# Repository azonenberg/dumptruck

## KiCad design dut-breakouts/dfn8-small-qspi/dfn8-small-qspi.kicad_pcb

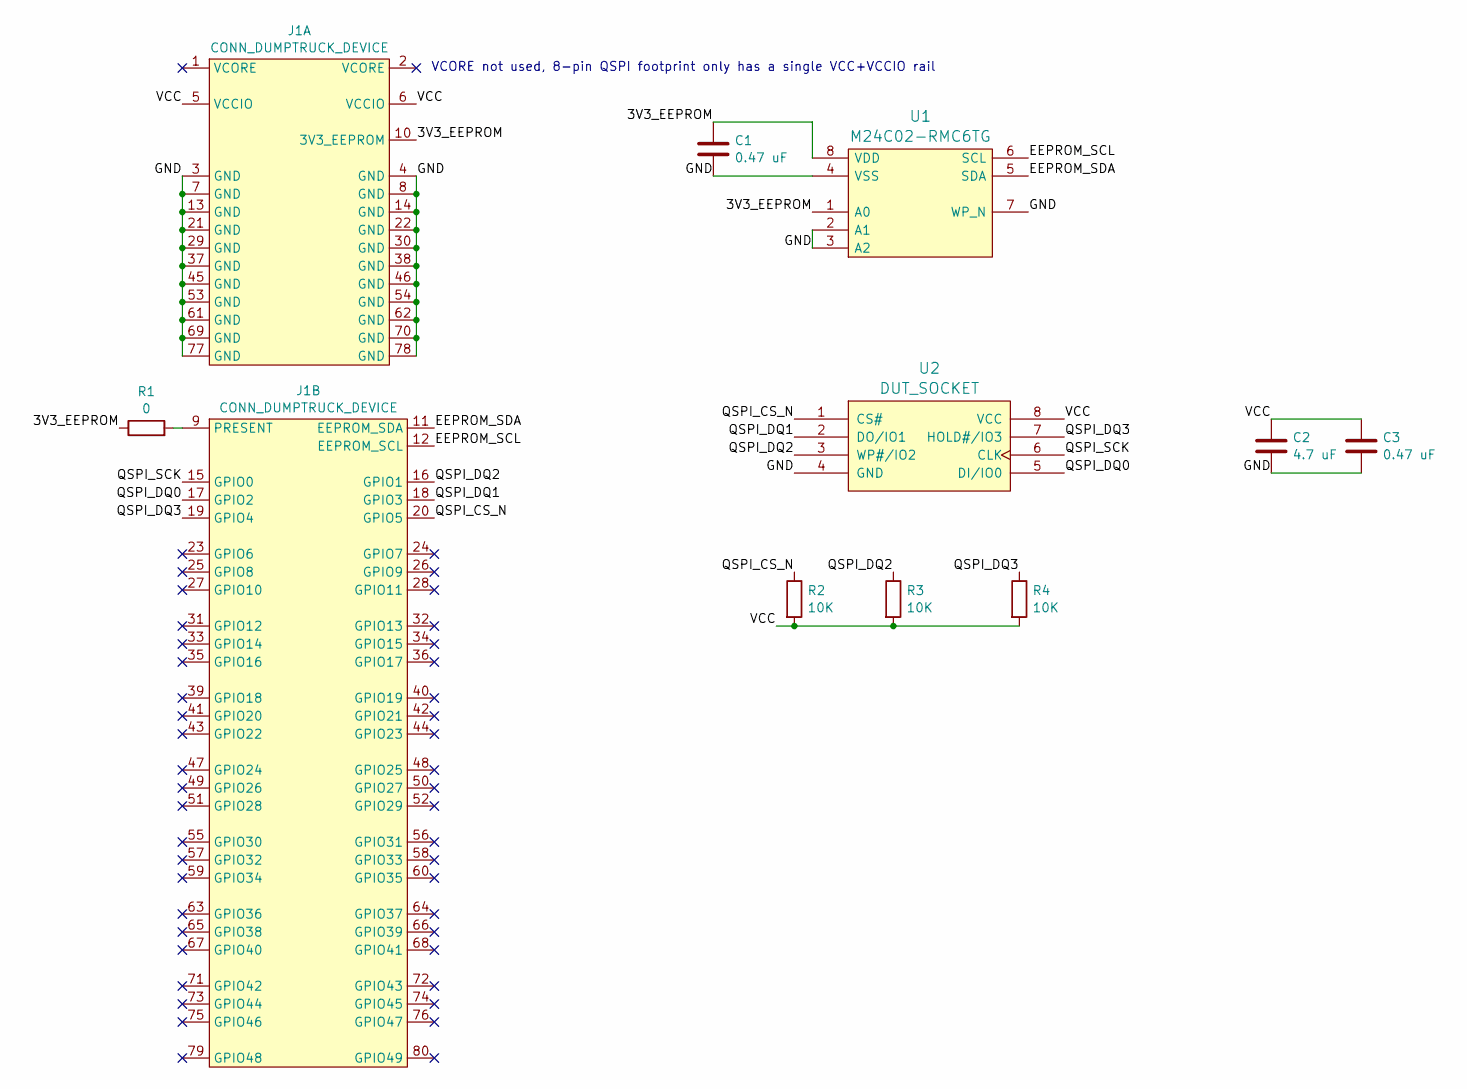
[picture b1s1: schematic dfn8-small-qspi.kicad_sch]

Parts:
C1, C3: 0.47 uF; EIA_0402_CAP_NOSILK
C2: 4.7 uF; EIA_0603_CAP_NOSILK
J1: CONN_DUMPTRUCK_DEVICE; CONN_SAMTEC_BSE-040-01-L-D-A-TR
R1: 0; EIA_0402_RES_NOSILK
R2, R3, R4: 10K; EIA_0402_RES_NOSILK
U1: M24C02-RMC6TG; DFN_8_0.5MM_2x3MM_TALL
U2: DUT_SOCKET; DFN_8_SOCKET_MOLDED_5x6MM

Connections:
/3V3_EEPROM: C1.1, J1.10 (3V3_EEPROM), R1.1, U1.1 (A0), U1.8 (VDD)
/EEPROM_SCL: J1.12 (EEPROM_SCL), U1.6 (SCL)
/EEPROM_SDA: J1.11 (EEPROM_SDA), U1.5 (SDA)
/GND: C1.2, C2.2, C3.2, J1.3 (GND), J1.4 (GND), J1.7 (GND), J1.8 (GND), J1.13 (GND), J1.14 (GND), J1.21 (GND), J1.22 (GND), J1.29 (GND), J1.30 (GND), J1.37 (GND), J1.38 (GND), J1.45 (GND), J1.46 (GND), J1.53 (GND), J1.54 (GND), J1.61 (GND), J1.62 (GND), J1.69 (GND), J1.70 (GND), J1.77 (GND), J1.78 (GND), U1.2 (A1), U1.3 (A2), U1.4 (VSS), U1.7 (WP_N), U2.4 (GND)
/QSPI_CS_N: J1.20 (GPIO5), R2.1, U2.1 (CS#)
/QSPI_DQ0: J1.17 (GPIO2), U2.5 (DI/IO0)
/QSPI_DQ1: J1.18 (GPIO3), U2.2 (DO/IO1)
/QSPI_DQ2: J1.16 (GPIO1), R3.1, U2.3 (WP#/IO2)
/QSPI_DQ3: J1.19 (GPIO4), R4.1, U2.7 (HOLD#/IO3)
/QSPI_SCK: J1.15 (GPIO0), U2.6 (CLK)
/VCC: C2.1, C3.1, J1.5 (VCCIO), J1.6 (VCCIO), R2.2, R3.2, R4.2, U2.8 (VCC)
unnamed: J1.9 (PRESENT), R1.2

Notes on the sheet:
VCORE not used, 8-pin QSPI footprint only has a single VCC+VCCIO rail

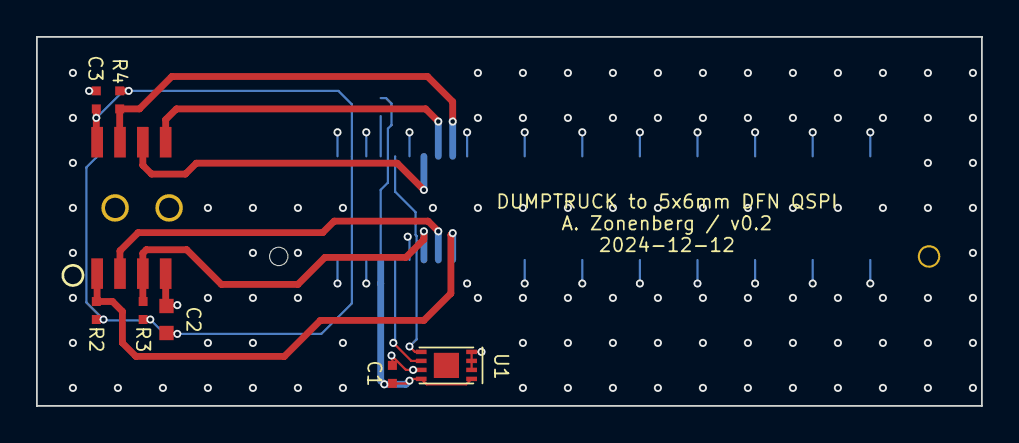
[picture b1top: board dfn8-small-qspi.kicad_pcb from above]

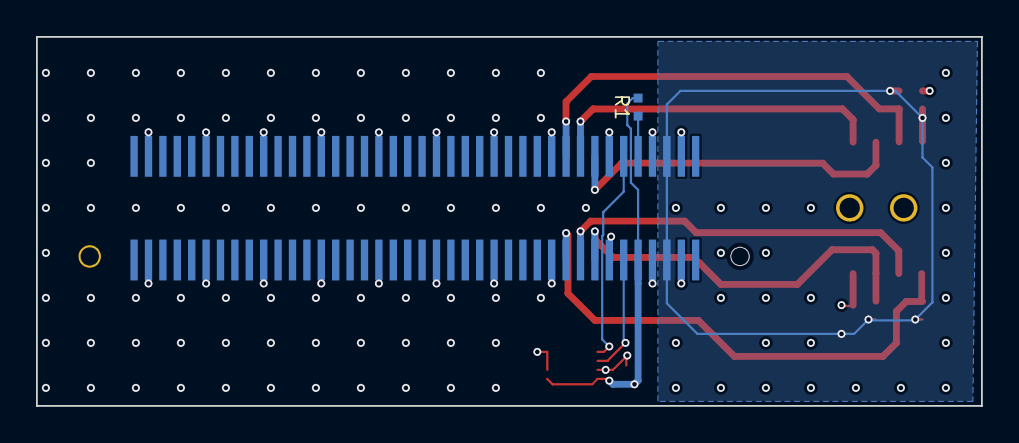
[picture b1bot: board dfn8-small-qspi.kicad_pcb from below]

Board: 4 copper layers, 52.5 x 20.5 mm, 10 parts (2 on the bottom side), 12 nets.

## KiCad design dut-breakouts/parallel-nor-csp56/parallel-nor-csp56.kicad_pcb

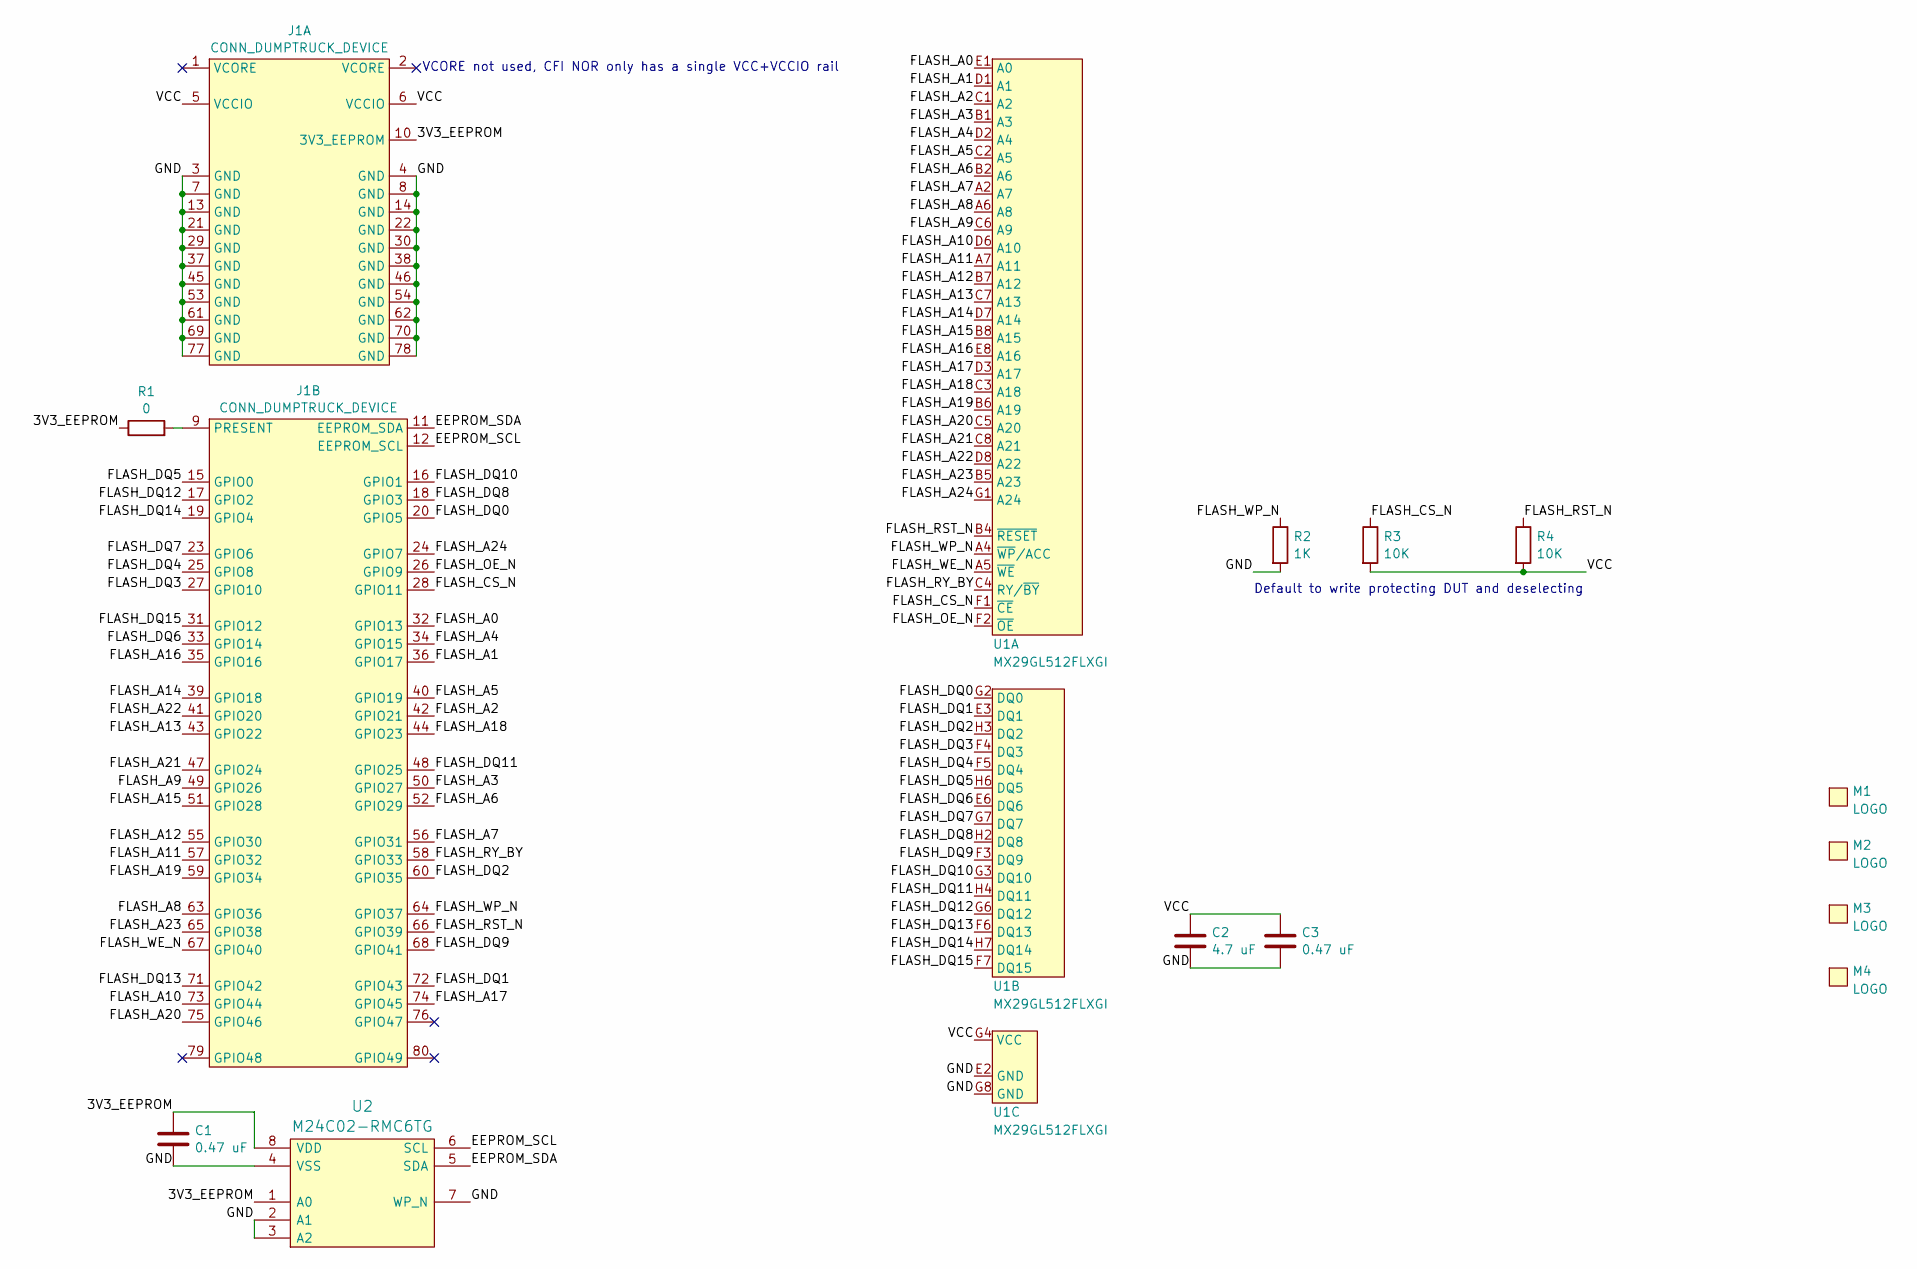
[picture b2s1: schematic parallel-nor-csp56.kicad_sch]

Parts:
C1, C3: 0.47 uF; EIA_0402_CAP_NOSILK
C2: 4.7 uF; EIA_0603_CAP_NOSILK
J1: CONN_DUMPTRUCK_DEVICE; CONN_SAMTEC_BSE-040-01-L-D-A-TR
M1: LOGO; LONGTHING-1200DPI
M2: LOGO; Logo_silk_ROHS_5x2.8mm
M3: LOGO; Logo_silk_OSHW_6x6mm
M4: LOGO; Logo_silk_WEEE_3.4x5mm
R1: 0; EIA_0402_RES_NOSILK
R2: 1K; EIA_0402_RES_NOSILK
R3, R4: 10K; EIA_0402_RES_NOSILK
U1: MX29GL512FLXGI; BGA_56_6x9_DEPOP_0.8MM_CFI_CSP
U2: M24C02-RMC6TG; DFN_8_0.5MM_2x3MM_TALL

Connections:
/3V3_EEPROM: C1.1, J1.10 (3V3_EEPROM), R1.1, U2.1 (A0), U2.8 (VDD)
/EEPROM_SCL: J1.12 (EEPROM_SCL), U2.6 (SCL)
/EEPROM_SDA: J1.11 (EEPROM_SDA), U2.5 (SDA)
/FLASH_A0: J1.32 (GPIO13), U1.E1 (A0)
/FLASH_A1: J1.36 (GPIO17), U1.D1 (A1)
/FLASH_A2: J1.42 (GPIO21), U1.C1 (A2)
/FLASH_A3: J1.50 (GPIO27), U1.B1 (A3)
/FLASH_A4: J1.34 (GPIO15), U1.D2 (A4)
/FLASH_A5: J1.40 (GPIO19), U1.C2 (A5)
/FLASH_A6: J1.52 (GPIO29), U1.B2 (A6)
/FLASH_A7: J1.56 (GPIO31), U1.A2 (A7)
/FLASH_A8: J1.63 (GPIO36), U1.A6 (A8)
/FLASH_A9: J1.49 (GPIO26), U1.C6 (A9)
/FLASH_A10: J1.73 (GPIO44), U1.D6 (A10)
/FLASH_A11: J1.57 (GPIO32), U1.A7 (A11)
/FLASH_A12: J1.55 (GPIO30), U1.B7 (A12)
/FLASH_A13: J1.43 (GPIO22), U1.C7 (A13)
/FLASH_A14: J1.39 (GPIO18), U1.D7 (A14)
/FLASH_A15: J1.51 (GPIO28), U1.B8 (A15)
/FLASH_A16: J1.35 (GPIO16), U1.E8 (A16)
/FLASH_A17: J1.74 (GPIO45), U1.D3 (A17)
/FLASH_A18: J1.44 (GPIO23), U1.C3 (A18)
/FLASH_A19: J1.59 (GPIO34), U1.B6 (A19)
/FLASH_A20: J1.75 (GPIO46), U1.C5 (A20)
/FLASH_A21: J1.47 (GPIO24), U1.C8 (A21)
/FLASH_A22: J1.41 (GPIO20), U1.D8 (A22)
/FLASH_A23: J1.65 (GPIO38), U1.B5 (A23)
/FLASH_A24: J1.24 (GPIO7), U1.G1 (A24)
/FLASH_CS_N: J1.28 (GPIO11), R3.1, U1.F1 (~CE)
/FLASH_DQ0: J1.20 (GPIO5), U1.G2 (DQ0)
/FLASH_DQ1: J1.72 (GPIO43), U1.E3 (DQ1)
/FLASH_DQ2: J1.60 (GPIO35), U1.H3 (DQ2)
/FLASH_DQ3: J1.27 (GPIO10), U1.F4 (DQ3)
/FLASH_DQ4: J1.25 (GPIO8), U1.F5 (DQ4)
/FLASH_DQ5: J1.15 (GPIO0), U1.H6 (DQ5)
/FLASH_DQ6: J1.33 (GPIO14), U1.E6 (DQ6)
/FLASH_DQ7: J1.23 (GPIO6), U1.G7 (DQ7)
/FLASH_DQ8: J1.18 (GPIO3), U1.H2 (DQ8)
/FLASH_DQ9: J1.68 (GPIO41), U1.F3 (DQ9)
/FLASH_DQ10: J1.16 (GPIO1), U1.G3 (DQ10)
/FLASH_DQ11: J1.48 (GPIO25), U1.H4 (DQ11)
/FLASH_DQ12: J1.17 (GPIO2), U1.G6 (DQ12)
/FLASH_DQ13: J1.71 (GPIO42), U1.F6 (DQ13)
/FLASH_DQ14: J1.19 (GPIO4), U1.H7 (DQ14)
/FLASH_DQ15: J1.31 (GPIO12), U1.F7 (DQ15)
/FLASH_OE_N: J1.26 (GPIO9), U1.F2 (~OE)
/FLASH_RST_N: J1.66 (GPIO39), R4.1, U1.B4 (~RESET)
/FLASH_RY_BY: J1.58 (GPIO33), U1.C4 (RY/~BY)
/FLASH_WE_N: J1.67 (GPIO40), U1.A5 (~WE)
/FLASH_WP_N: J1.64 (GPIO37), R2.1, U1.A4 (~WP/ACC)
/GND: C1.2, C2.2, C3.2, J1.3 (GND), J1.4 (GND), J1.7 (GND), J1.8 (GND), J1.13 (GND), J1.14 (GND), J1.21 (GND), J1.22 (GND), J1.29 (GND), J1.30 (GND), J1.37 (GND), J1.38 (GND), J1.45 (GND), J1.46 (GND), J1.53 (GND), J1.54 (GND), J1.61 (GND), J1.62 (GND), J1.69 (GND), J1.70 (GND), J1.77 (GND), J1.78 (GND), R2.2, U1.E2 (GND), U1.G8 (GND), U2.2 (A1), U2.3 (A2), U2.4 (VSS), U2.7 (WP_N)
/VCC: C2.1, C3.1, J1.5 (VCCIO), J1.6 (VCCIO), R3.2, R4.2, U1.G4 (VCC)
unnamed: J1.9 (PRESENT), R1.2

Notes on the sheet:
VCORE not used, CFI NOR only has a single VCC+VCCIO rail
Default to write protecting DUT and deselecting

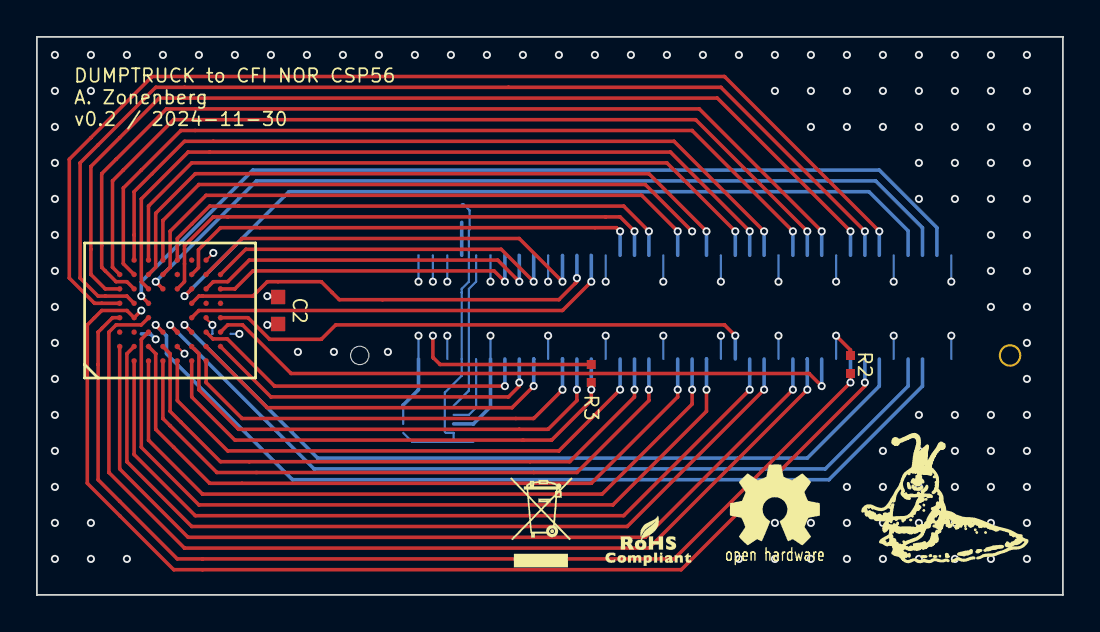
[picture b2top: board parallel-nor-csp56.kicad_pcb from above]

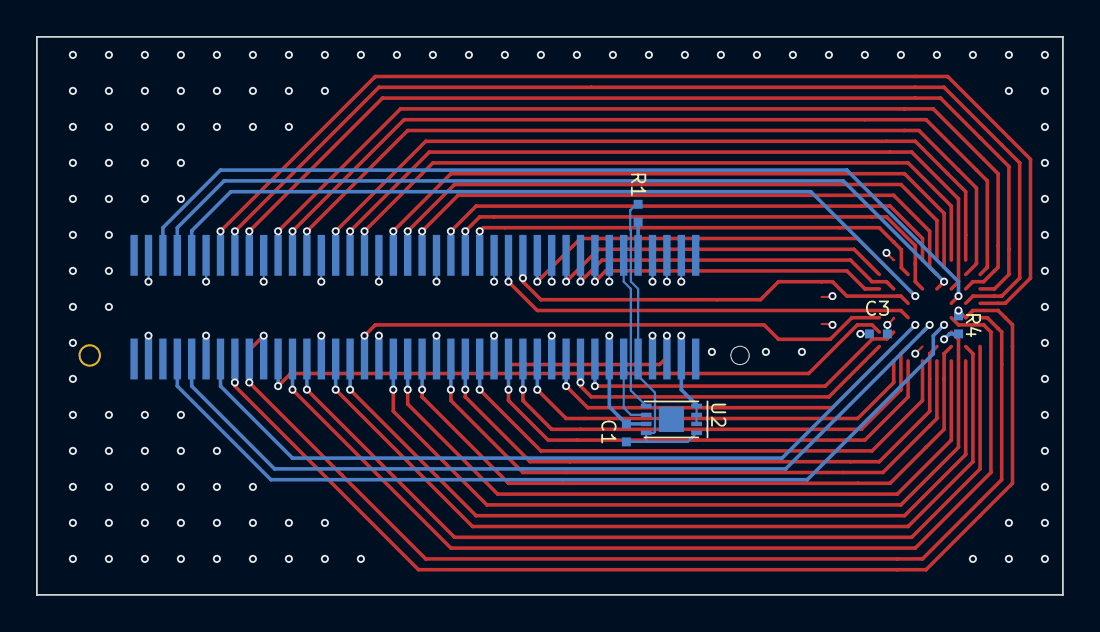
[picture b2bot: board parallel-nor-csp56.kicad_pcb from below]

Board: 4 copper layers, 57.0 x 31.0 mm, 14 parts (6 on the bottom side), 53 nets.

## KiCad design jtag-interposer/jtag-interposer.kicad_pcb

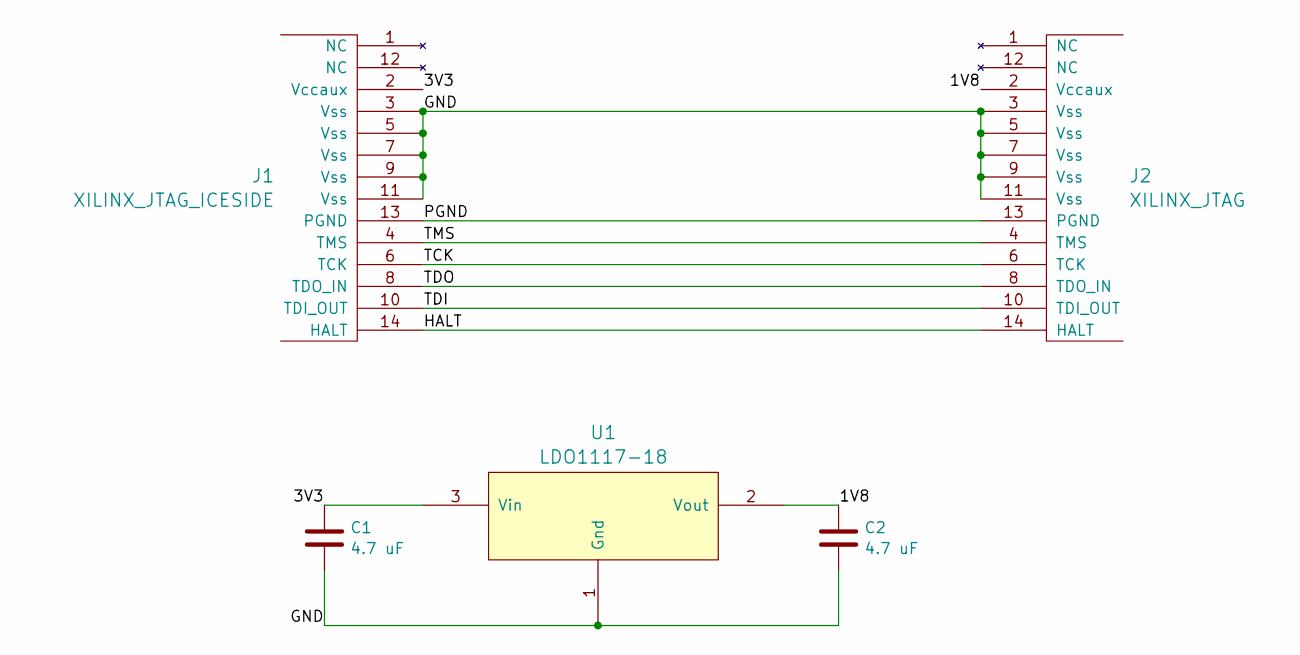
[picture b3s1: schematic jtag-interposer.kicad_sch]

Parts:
C1, C2: 4.7 uF; EIA_0603_CAP_NOSILK
J1: XILINX_JTAG_ICESIDE; XILINX_JTAG_PTH_MOLEX_0878311420
J2: XILINX_JTAG; XILINX_JTAG_PTH_MOLEX_0878311420
U1: LDO1117-18; SOT223-4

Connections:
/1V8: C2.1, J2.2 (Vccaux), U1.2 (Vout)
/3V3: C1.1, J1.2 (Vccaux), U1.3 (Vin)
/GND: C1.2, C2.2, J1.3 (Vss), J1.5 (Vss), J1.7 (Vss), J1.9 (Vss), J1.11 (Vss), J2.3 (Vss), J2.5 (Vss), J2.7 (Vss), J2.9 (Vss), J2.11 (Vss), U1.1 (Gnd)
/HALT: J1.14 (HALT), J2.14 (HALT)
/PGND: J1.13 (PGND), J2.13 (PGND)
/TCK: J1.6 (TCK), J2.6 (TCK)
/TDI: J1.10 (TDI_OUT), J2.10 (TDI_OUT)
/TDO: J1.8 (TDO_IN), J2.8 (TDO_IN)
/TMS: J1.4 (TMS), J2.4 (TMS)

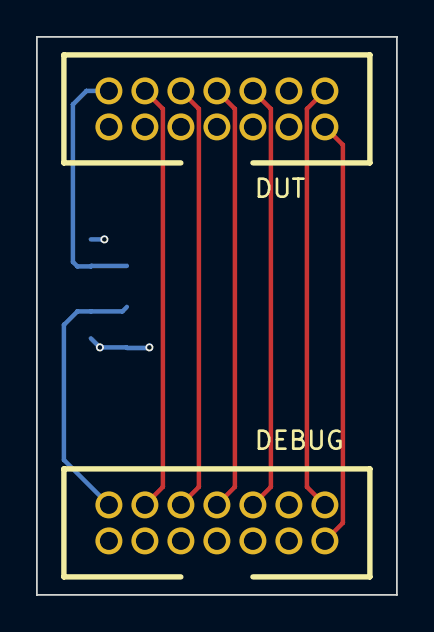
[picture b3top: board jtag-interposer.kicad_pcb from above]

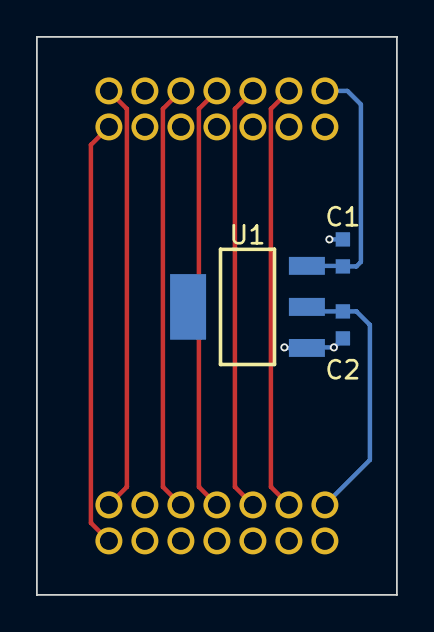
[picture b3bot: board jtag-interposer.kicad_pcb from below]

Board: 4 copper layers, 20.0 x 31.0 mm, 5 parts (3 on the bottom side), 9 nets.

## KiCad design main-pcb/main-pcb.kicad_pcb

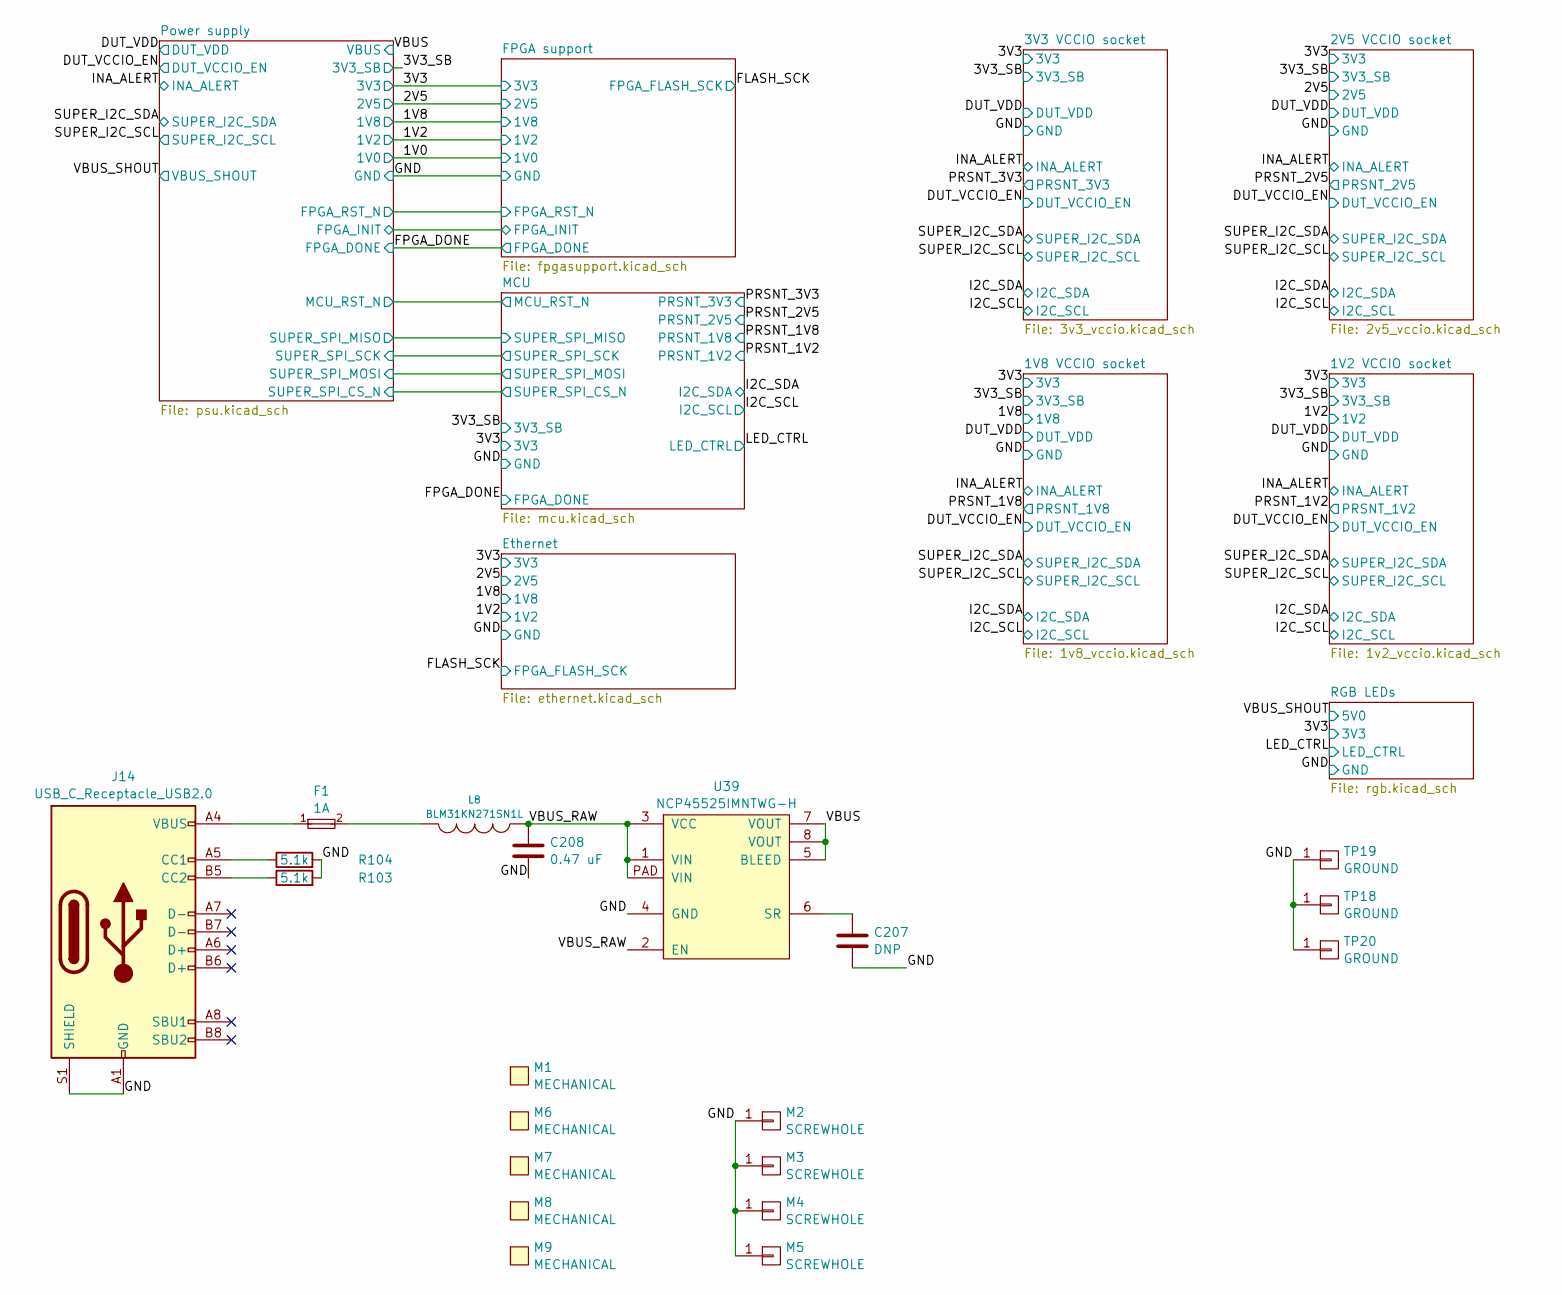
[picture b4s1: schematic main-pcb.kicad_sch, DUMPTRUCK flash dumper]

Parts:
C207: DNP; EIA_0402_CAP_NOSILK
C208: 0.47 uF; EIA_0402_CAP_NOSILK
F1: 1A; EIA_0402_RES_NOSILK
J14: USB_C_Receptacle_USB2.0; GCT_USB4500-03-0-A
L8: BLM31KN271SN1L; EIA_1206_CAP_NOSILK
M1: MECHANICAL; LONGTHING-1200DPI
M2, M3, M4, M5: SCREWHOLE; MECHANICAL_CLEARANCEHOLE_4_40
M6: MECHANICAL; LOGO_ESD_SENSITIVE_7MM
M7: MECHANICAL; Logo_silk_OSHW_6x6mm
M8: MECHANICAL; Logo_silk_ROHS_5x2.8mm
M9: MECHANICAL; Logo_silk_WEEE_3.4x5mm
R103, R104: 5.1k; EIA_0402_RES_NOSILK
TP18, TP19, TP20: GROUND; TESTPOINT_SMT_KEYSTONE_5016
U39: NCP45525IMNTWG-H; DFN_8_0.5MM_2x2MM

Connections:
/GND: C207.2, C208.2, J14.A1 (GND), J14.A12 (GND), J14.B1 (GND), J14.B12 (GND), J14.S1 (SHIELD), M2.1, M3.1, M4.1, M5.1, R103.2, R104.2, TP18.1, TP19.1, TP20.1, U39.4 (GND); also elsewhere on the board
/VBUS: U39.5 (BLEED), U39.7 (VOUT), U39.8 (VOUT); also elsewhere on the board
/VBUS_RAW: C208.1, L8.1, U39.1 (VIN), U39.2 (EN), U39.3 (VCC), U39.PAD (VIN)
unnamed: F1.1, J14.A4 (VBUS), J14.A9 (VBUS), J14.B4 (VBUS), J14.B9 (VBUS)
unnamed: F1.2, L8.2
unnamed: J14.A5 (CC1), R104.1
unnamed: J14.B5 (CC2), R103.1
unnamed: C207.1, U39.6 (SR)

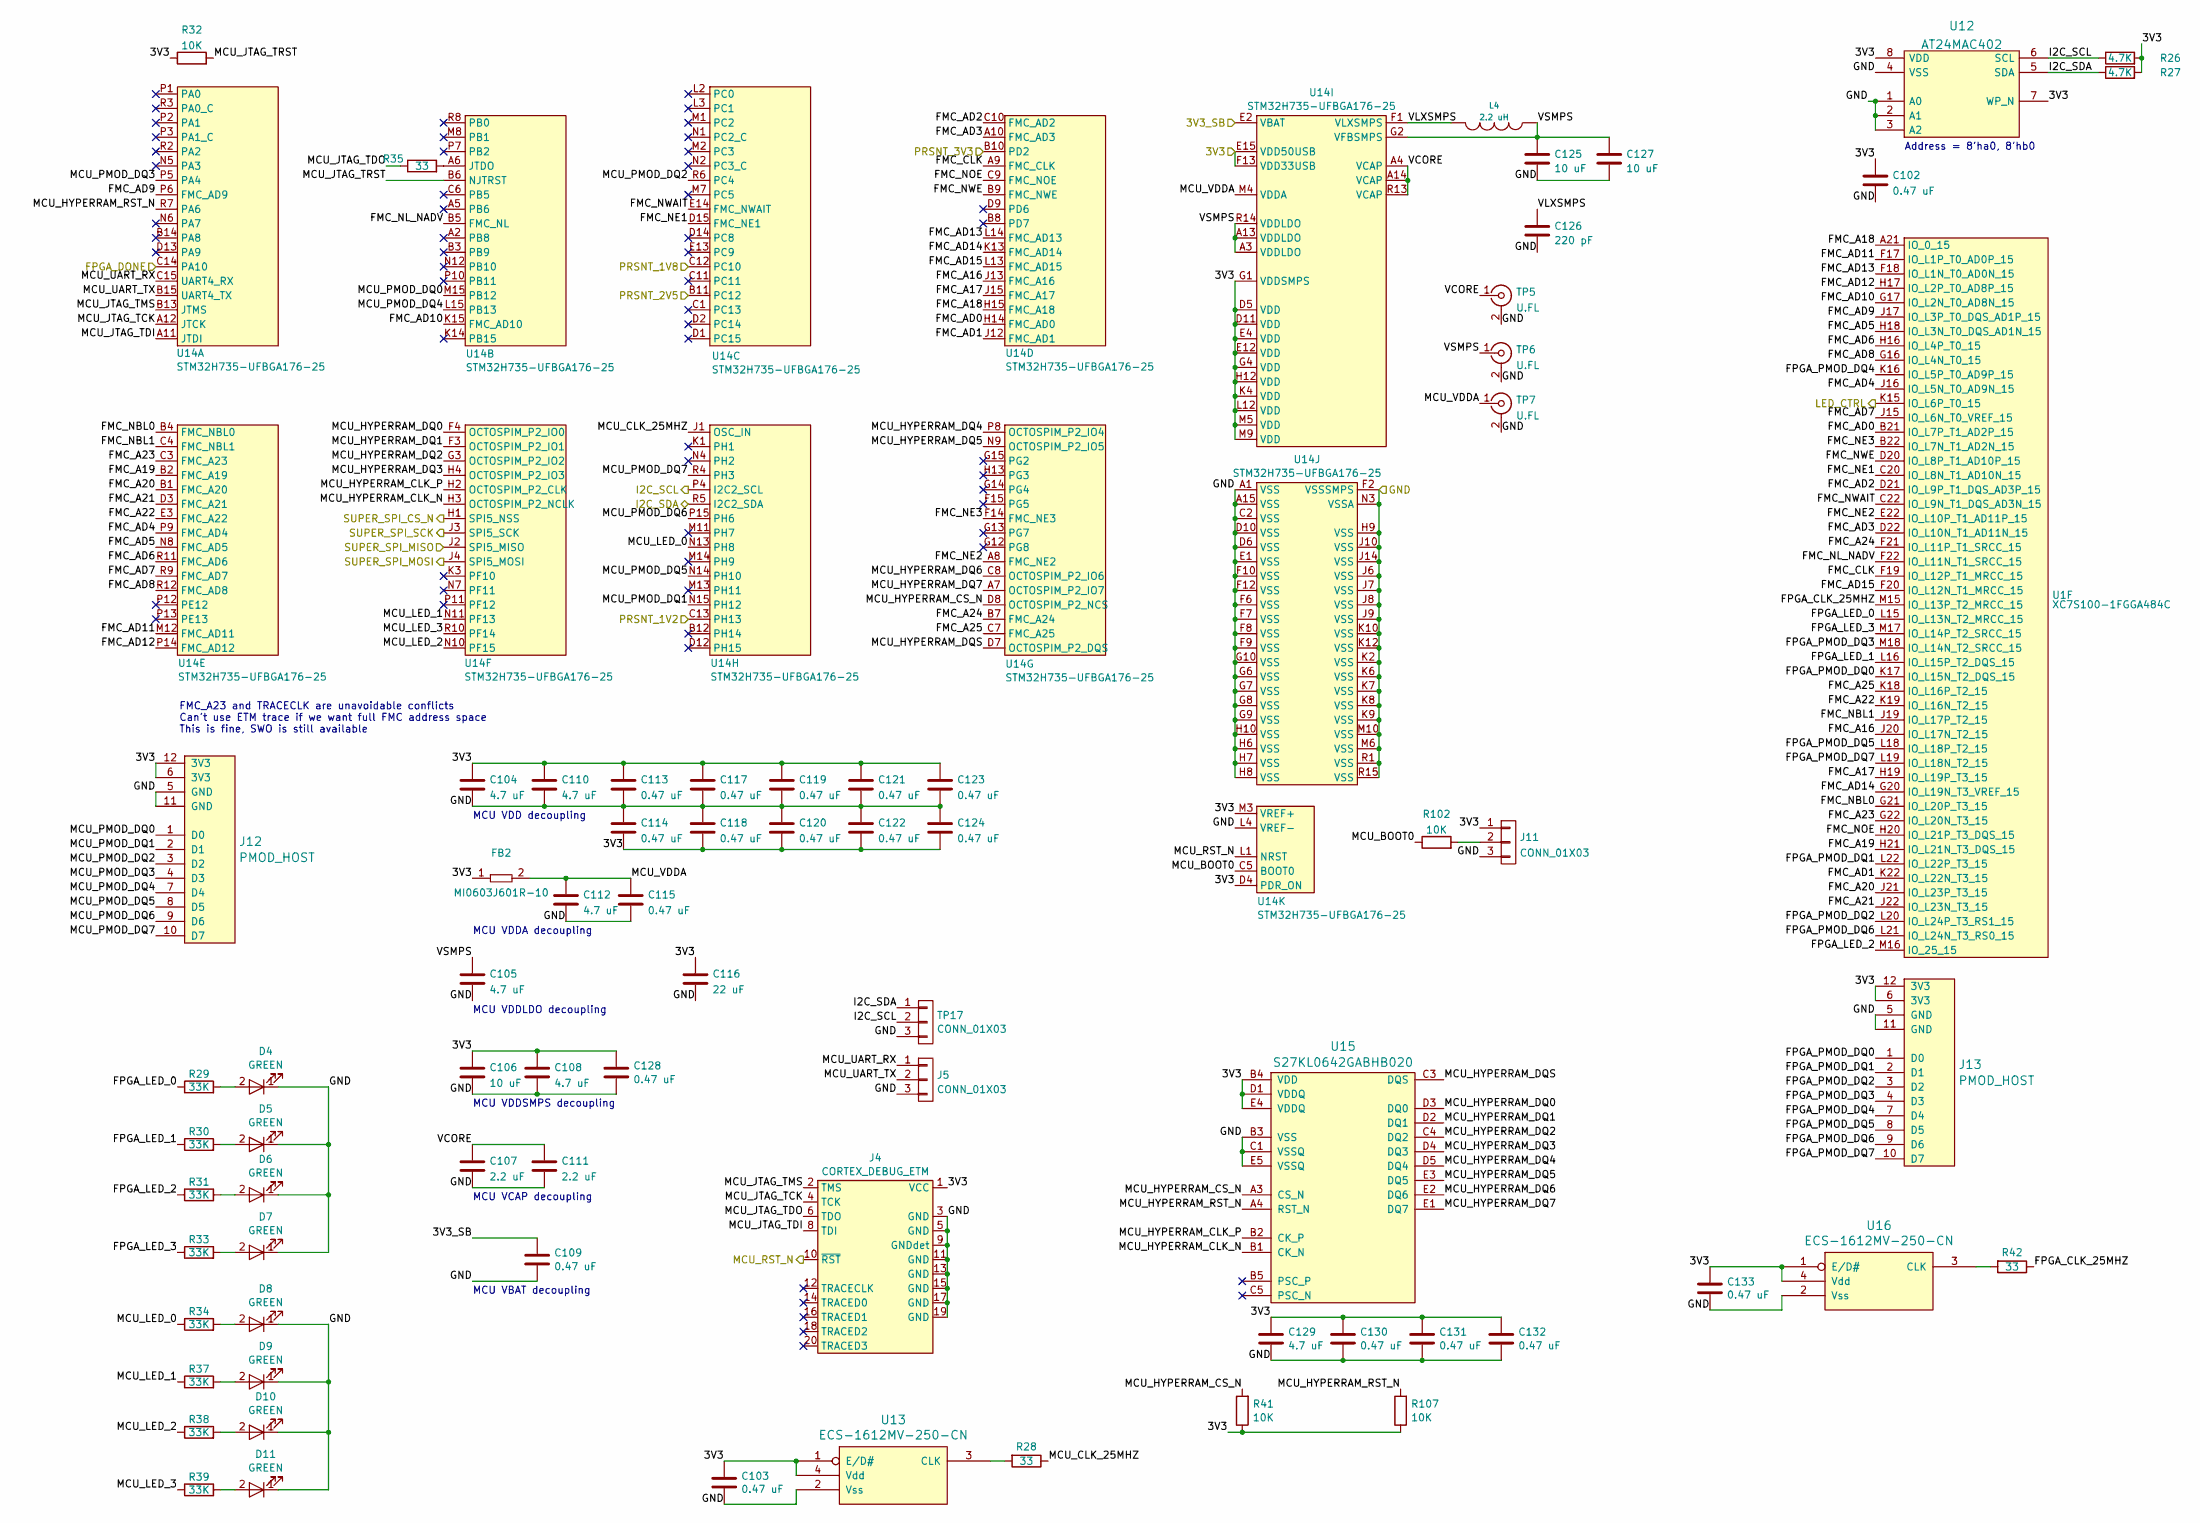
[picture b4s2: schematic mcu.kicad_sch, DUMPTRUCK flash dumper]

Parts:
C102, C103, C109, C113, C114, C115, C117, C118, C119, C120, C121, C122, C123, C124, C128, C130, C131, C132, C133: 0.47 uF; EIA_0402_CAP_NOSILK
C104, C105, C108, C110, C112, C129: 4.7 uF; EIA_0603_CAP_NOSILK
C106, C125, C127: 10 uF; EIA_0805_CAP_NOSILK
C107, C111: 2.2 uF; EIA_0805_CAP_NOSILK
C116: 22 uF; EIA_0805_CAP_NOSILK
C126: 220 pF; EIA_0402_CAP_NOSILK
D4, D5, D6, D7, D8, D9, D10, D11: GREEN; EIA_0402_LED
FB2: MI0603J601R-10; EIA_0603_INDUCTOR_NOSILK
J4: CORTEX_DEBUG_ETM; CONN_HEADER_1.27MM_2x10_SMT_SAMTEC_FTSH-110-01-L-DV-K
J5, J11: CONN_01X03; CONN_HEADER_2.54MM_1x3
J12, J13: PMOD_HOST; CONN_HEADER_2.54MM_2x6_RA_PMOD_HOST
L4: 2.2 uH; EIA_1210_CAP_NOSILK
R26, R27: 4.7K; EIA_0402_RES_NOSILK
R28, R35, R42: 33; EIA_0402_RES_NOSILK
R29, R30, R31, R33, R34, R37, R38, R39: 33K; EIA_0402_RES_NOSILK
R32, R41, R102, R107: 10K; EIA_0402_RES_NOSILK
TP5, TP6, TP7: U.FL; CONN_U.FL_TE_1909763-1
TP17: CONN_01X03; CONN_HEADER_2.54MM_1x3
U1: XC7S100-1FGGA484C; BGA_484_22x22_FULLARRAY_1MM
U12: AT24MAC402; DFN_8_0.5MM_2x3MM_TALL
U13, U16: ECS-1612MV-250-CN; OSCILLATOR_1.6x1.2
U14: STM32H735-UFBGA176-25; BGA_201_10x10_DEPOP_0.65MM_OSHPARK
U15: S27KL0642GABHB020; BGA_24_6x8_DEPOP1_1MM

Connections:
/3V3: C102.1, C103.1, C104.1, C106.1, C108.1, C110.1, C113.1, C114.2, C116.1, C117.1, C118.2, C119.1, C120.2, C121.1, C122.2, C123.1, C124.2, C128.1, C129.1, C130.1, C131.1, C132.1, C133.1, FB2.1, J4.1 (VCC), J11.1, J12.6 (3V3), J12.12 (3V3), J13.6 (3V3), J13.12 (3V3), R26.2, R27.2, R32.1, R41.1, R107.1, U12.7 (WP_N), U12.8 (VDD), U13.1 (E/D#), U13.4 (Vdd), U14.D4 (PDR_ON), U14.D5 (VDD), U14.D11 (VDD), U14.E4 (VDD), U14.E12 (VDD), U14.E15 (VDD50USB), U14.F13 (VDD33USB), U14.G1 (VDDSMPS), U14.G4 (VDD), U14.H12 (VDD), U14.K4 (VDD), U14.L12 (VDD), U14.M3 (VREF+), U14.M5 (VDD), U14.M9 (VDD), U15.B4 (VDD), U15.D1 (VDDQ), U15.E4 (VDDQ), U16.1 (E/D#), U16.4 (Vdd); also elsewhere on the board
/3V3_SB: C109.1, U14.E2 (VBAT); also elsewhere on the board
/FPGA_DONE: U14.C14 (PA10); also elsewhere on the board
/GND: C102.2, C103.2, C104.2, C105.2, C106.2, C107.2, C108.2, C109.2, C110.2, C111.2, C112.2, C113.2, C114.1, C115.2, C116.2, C117.2, C118.1, C119.2, C120.1, C121.2, C122.1, C123.2, C124.1, C125.2, C126.2, C127.2, C128.2, C129.2, C130.2, C131.2, C132.2, C133.2, D4.1 (K), D5.1 (K), D6.1 (K), D7.1 (K), D8.1 (K), D9.1 (K), D10.1 (K), D11.1 (K), J4.3 (GND), J4.5 (GND), J4.9 (GNDdet), J4.11 (GND), J4.13 (GND), J4.15 (GND), J4.17 (GND), J4.19 (GND), J5.3, J11.3, J12.5 (GND), J12.11 (GND), J13.5 (GND), J13.11 (GND), TP5.2 (Ext), TP6.2 (Ext), TP7.2 (Ext), TP17.3, U12.1 (A0), U12.2 (A1), U12.3 (A2), U12.4 (VSS), U13.2 (Vss), U14.A1 (VSS), U14.A15 (VSS), U14.C2 (VSS), U14.D6 (VSS), U14.D10 (VSS), U14.E1 (VSS), U14.F2 (VSSSMPS), U14.F6 (VSS), U14.F7 (VSS), U14.F8 (VSS), U14.F9 (VSS), U14.F10 (VSS), U14.F12 (VSS), U14.G6 (VSS), U14.G7 (VSS), U14.G8 (VSS), U14.G9 (VSS), U14.G10 (VSS), U14.H6 (VSS), U14.H7 (VSS), U14.H8 (VSS), U14.H9 (VSS), U14.H10 (VSS), U14.J6 (VSS), U14.J7 (VSS), U14.J8 (VSS), U14.J9 (VSS), U14.J10 (VSS), U14.J14 (VSS), U14.K2 (VSS), U14.K6 (VSS), U14.K7 (VSS), U14.K8 (VSS), U14.K9 (VSS), U14.K10 (VSS), U14.K12 (VSS), U14.L4 (VREF-), U14.M6 (VSS), U14.M10 (VSS), U14.N3 (VSSA), U14.R1 (VSS), U14.R15 (VSS), U15.B3 (VSS), U15.C1 (VSSQ), U15.E5 (VSSQ), U16.2 (Vss); also elsewhere on the board
/I2C_SCL: R26.1, TP17.2, U12.6 (SCL), U14.P4 (I2C2_SCL); also elsewhere on the board
/I2C_SDA: R27.1, TP17.1, U12.5 (SDA), U14.R5 (I2C2_SDA); also elsewhere on the board
/LED_CTRL: U1.K15 (IO_L6P_T0_15); also elsewhere on the board
/MCU/FMC_A16: U1.J20 (IO_L17N_T2_15), U14.J13 (FMC_A16)
/MCU/FMC_A17: U1.H19 (IO_L19P_T3_15), U14.J15 (FMC_A17)
/MCU/FMC_A18: U1.A21 (IO_0_15), U14.H15 (FMC_A18)
/MCU/FMC_A19: U1.H21 (IO_L21N_T3_DQS_15), U14.B2 (FMC_A19)
/MCU/FMC_A20: U1.J21 (IO_L23P_T3_15), U14.B1 (FMC_A20)
/MCU/FMC_A21: U1.J22 (IO_L23N_T3_15), U14.D3 (FMC_A21)
/MCU/FMC_A22: U1.K19 (IO_L16N_T2_15), U14.E3 (FMC_A22)
/MCU/FMC_A23: U1.G22 (IO_L20N_T3_15), U14.C3 (FMC_A23)
/MCU/FMC_A24: U1.F21 (IO_L11P_T1_SRCC_15), U14.B7 (FMC_A24)
/MCU/FMC_A25: U1.K18 (IO_L16P_T2_15), U14.C7 (FMC_A25)
/MCU/FMC_AD0: U1.B21 (IO_L7P_T1_AD2P_15), U14.H14 (FMC_AD0)
/MCU/FMC_AD1: U1.K22 (IO_L22N_T3_15), U14.J12 (FMC_AD1)
/MCU/FMC_AD2: U1.D21 (IO_L9P_T1_DQS_AD3P_15), U14.C10 (FMC_AD2)
/MCU/FMC_AD3: U1.D22 (IO_L10N_T1_AD11N_15), U14.A10 (FMC_AD3)
/MCU/FMC_AD4: U1.J16 (IO_L5N_T0_AD9N_15), U14.P9 (FMC_AD4)
/MCU/FMC_AD5: U1.H18 (IO_L3N_T0_DQS_AD1N_15), U14.N8 (FMC_AD5)
/MCU/FMC_AD6: U1.H16 (IO_L4P_T0_15), U14.R11 (FMC_AD6)
/MCU/FMC_AD7: U1.J15 (IO_L6N_T0_VREF_15), U14.R9 (FMC_AD7)
/MCU/FMC_AD8: U1.G16 (IO_L4N_T0_15), U14.R12 (FMC_AD8)
/MCU/FMC_AD9: U1.J17 (IO_L3P_T0_DQS_AD1P_15), U14.P6 (FMC_AD9)
/MCU/FMC_AD10: U1.G17 (IO_L2N_T0_AD8N_15), U14.K15 (FMC_AD10)
/MCU/FMC_AD11: U1.F17 (IO_L1P_T0_AD0P_15), U14.M12 (FMC_AD11)
/MCU/FMC_AD12: U1.H17 (IO_L2P_T0_AD8P_15), U14.P14 (FMC_AD12)
/MCU/FMC_AD13: U1.F18 (IO_L1N_T0_AD0N_15), U14.L14 (FMC_AD13)
/MCU/FMC_AD14: U1.G20 (IO_L19N_T3_VREF_15), U14.K13 (FMC_AD14)
/MCU/FMC_AD15: U1.F20 (IO_L12N_T1_MRCC_15), U14.L13 (FMC_AD15)
/MCU/FMC_CLK: U1.F19 (IO_L12P_T1_MRCC_15), U14.A9 (FMC_CLK)
/MCU/FMC_NBL0: U1.G21 (IO_L20P_T3_15), U14.B4 (FMC_NBL0)
/MCU/FMC_NBL1: U1.J19 (IO_L17P_T2_15), U14.C4 (FMC_NBL1)
/MCU/FMC_NE1: U1.C20 (IO_L8N_T1_AD10N_15), U14.D15 (FMC_NE1)
/MCU/FMC_NE2: U1.E22 (IO_L10P_T1_AD11P_15), U14.A8 (FMC_NE2)
/MCU/FMC_NE3: U1.B22 (IO_L7N_T1_AD2N_15), U14.F14 (FMC_NE3)
/MCU/FMC_NL_NADV: U1.F22 (IO_L11N_T1_SRCC_15), U14.B5 (FMC_NL)
/MCU/FMC_NOE: U1.H20 (IO_L21P_T3_DQS_15), U14.C9 (FMC_NOE)
/MCU/FMC_NWAIT: U1.C22 (IO_L9N_T1_DQS_AD3N_15), U14.E14 (FMC_NWAIT)
/MCU/FMC_NWE: U1.D20 (IO_L8P_T1_AD10P_15), U14.B9 (FMC_NWE)
/MCU/FPGA_CLK_25MHZ: R42.1, U1.M15 (IO_L13P_T2_MRCC_15)
/MCU/FPGA_LED_0: R29.1, U1.L15 (IO_L13N_T2_MRCC_15)
/MCU/FPGA_LED_1: R30.1, U1.L16 (IO_L15P_T2_DQS_15)
/MCU/FPGA_LED_2: R31.1, U1.M16 (IO_25_15)
/MCU/FPGA_LED_3: R33.1, U1.M17 (IO_L14P_T2_SRCC_15)
/MCU/FPGA_PMOD_DQ0: J13.1 (D0), U1.K17 (IO_L15N_T2_DQS_15)
/MCU/FPGA_PMOD_DQ1: J13.2 (D1), U1.L22 (IO_L22P_T3_15)
/MCU/FPGA_PMOD_DQ2: J13.3 (D2), U1.L20 (IO_L24P_T3_RS1_15)
/MCU/FPGA_PMOD_DQ3: J13.4 (D3), U1.M18 (IO_L14N_T2_SRCC_15)
/MCU/FPGA_PMOD_DQ4: J13.7 (D4), U1.K16 (IO_L5P_T0_AD9P_15)
/MCU/FPGA_PMOD_DQ5: J13.8 (D5), U1.L18 (IO_L18P_T2_15)
/MCU/FPGA_PMOD_DQ6: J13.9 (D6), U1.L21 (IO_L24N_T3_RS0_15)
/MCU/FPGA_PMOD_DQ7: J13.10 (D7), U1.L19 (IO_L18N_T2_15)
/MCU/MCU_BOOT0: R102.1, U14.C5 (BOOT0)
/MCU/MCU_CLK_25MHZ: R28.1, U14.J1 (OSC_IN)
/MCU/MCU_HYPERRAM_CLK_N: U14.H3 (OCTOSPIM_P2_NCLK), U15.B1 (CK_N)
/MCU/MCU_HYPERRAM_CLK_P: U14.H2 (OCTOSPIM_P2_CLK), U15.B2 (CK_P)
/MCU/MCU_HYPERRAM_CS_N: R41.2, U14.D8 (OCTOSPIM_P2_NCS), U15.A3 (CS_N)
/MCU/MCU_HYPERRAM_DQ0: U14.F4 (OCTOSPIM_P2_IO0), U15.D3 (DQ0)
/MCU/MCU_HYPERRAM_DQ1: U14.F3 (OCTOSPIM_P2_IO1), U15.D2 (DQ1)
/MCU/MCU_HYPERRAM_DQ2: U14.G3 (OCTOSPIM_P2_IO2), U15.C4 (DQ2)
/MCU/MCU_HYPERRAM_DQ3: U14.H4 (OCTOSPIM_P2_IO3), U15.D4 (DQ3)
/MCU/MCU_HYPERRAM_DQ4: U14.P8 (OCTOSPIM_P2_IO4), U15.D5 (DQ4)
/MCU/MCU_HYPERRAM_DQ5: U14.N9 (OCTOSPIM_P2_IO5), U15.E3 (DQ5)
/MCU/MCU_HYPERRAM_DQ6: U14.C8 (OCTOSPIM_P2_IO6), U15.E2 (DQ6)
/MCU/MCU_HYPERRAM_DQ7: U14.A7 (OCTOSPIM_P2_IO7), U15.E1 (DQ7)
/MCU/MCU_HYPERRAM_DQS: U14.D7 (OCTOSPIM_P2_DQS), U15.C3 (DQS)
/MCU/MCU_HYPERRAM_RST_N: R107.2, U14.R7 (PA6), U15.A4 (RST_N)
/MCU/MCU_JTAG_TCK: J4.4 (TCK), U14.A12 (JTCK)
/MCU/MCU_JTAG_TDI: J4.8 (TDI), U14.A11 (JTDI)
/MCU/MCU_JTAG_TDO: J4.6 (TDO), R35.1
/MCU/MCU_JTAG_TMS: J4.2 (TMS), U14.B13 (JTMS)
/MCU/MCU_JTAG_TRST: R32.2, U14.B6 (NJTRST)
/MCU/MCU_LED_0: R34.1, U14.N13 (PH8)
/MCU/MCU_LED_1: R37.1, U14.N11 (PF13)
/MCU/MCU_LED_2: R38.1, U14.N10 (PF15)
/MCU/MCU_LED_3: R39.1, U14.R10 (PF14)
/MCU/MCU_PMOD_DQ0: J12.1 (D0), U14.M15 (PB12)
/MCU/MCU_PMOD_DQ1: J12.2 (D1), U14.N15 (PH12)
/MCU/MCU_PMOD_DQ2: J12.3 (D2), U14.R6 (PC4)
/MCU/MCU_PMOD_DQ3: J12.4 (D3), U14.P5 (PA4)
/MCU/MCU_PMOD_DQ4: J12.7 (D4), U14.L15 (PB13)
/MCU/MCU_PMOD_DQ5: J12.8 (D5), U14.N14 (PH10)
/MCU/MCU_PMOD_DQ6: J12.9 (D6), U14.P15 (PH6)
/MCU/MCU_PMOD_DQ7: J12.10 (D7), U14.R4 (PH3)
/MCU/MCU_RST_N: J4.10 (~RST), U14.L1 (NRST); also elsewhere on the board
/MCU/MCU_UART_RX: J5.1, U14.C15 (UART4_RX)
/MCU/MCU_UART_TX: J5.2, U14.B15 (UART4_TX)
/MCU/MCU_VDDA: C112.1, C115.1, FB2.2, TP7.1 (In), U14.M4 (VDDA)
/MCU/SUPER_SPI_CS_N: U14.H1 (SPI5_NSS); also elsewhere on the board
/MCU/SUPER_SPI_MISO: U14.J2 (SPI5_MISO); also elsewhere on the board
/MCU/SUPER_SPI_MOSI: U14.J4 (SPI5_MOSI); also elsewhere on the board
/MCU/SUPER_SPI_SCK: U14.J3 (SPI5_SCK); also elsewhere on the board
/MCU/VCORE: C107.1, C111.1, TP5.1 (In), U14.A4 (VCAP), U14.A14 (VCAP), U14.R13 (VCAP)
/MCU/VLXSMPS: C126.1, L4.2, U14.F1 (VLXSMPS)
/MCU/VSMPS: C105.1, C125.1, C127.1, L4.1, TP6.1 (In), U14.A3 (VDDLDO), U14.A13 (VDDLDO), U14.G2 (VFBSMPS), U14.R14 (VDDLDO)
/PRSNT_1V2: U14.C13 (PH13); also elsewhere on the board
/PRSNT_1V8: U14.C12 (PC10); also elsewhere on the board
/PRSNT_2V5: U14.B11 (PC12); also elsewhere on the board
/PRSNT_3V3: U14.B10 (PD2); also elsewhere on the board
unnamed: D4.2 (A), R29.2
unnamed: D5.2 (A), R30.2
unnamed: D6.2 (A), R31.2
unnamed: D7.2 (A), R33.2
unnamed: D8.2 (A), R34.2
unnamed: D9.2 (A), R37.2
unnamed: D10.2 (A), R38.2
unnamed: D11.2 (A), R39.2
unnamed: J11.2, R102.2
unnamed: R28.2, U13.3 (CLK)
unnamed: R35.2, U14.A6 (JTDO)
unnamed: R42.2, U16.3 (CLK)

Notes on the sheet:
MCU VDDLDO decoupling
MCU VDD decoupling
MCU VDDSMPS decoupling
MCU VDDA decoupling
MCU VCAP decoupling
Address = 8'ha0, 8'hb0
MCU VBAT decoupling
FMC_A23 and TRACECLK are unavoidable conflicts Can't use ETM trace if we want full FMC address space This is fine, SWO is still available
